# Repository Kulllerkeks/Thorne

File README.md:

# Thorne keyboard

The Thorne keyboard is a split keyboard with 3x6 column staggered keys 
and 3 thumb keys, a variation of the [Corne](https://github.com/foostan/crkbd) Keyboard.

## Lineup

- corne-classic
  ([JP](corne-classic/doc/buildguide_jp.md)/[EN](corne-classic/doc/buildguide_en.md)):
  Corne for Cherry MX switches
- corne-cherry
  ([JP](corne-cherry/doc/buildguide_jp.md)/[EN](corne-cherry/doc/buildguide_en.md))
  ([tilting, JP](corne-cherry/doc/v2/buildguide_tilting_tenting_plate_jp.md)/[tilting, EN](corne-cherry/doc/v2/buildguide_tilting_tenting_plate_en.md)):
  Hotswappable Corne for Cherry MX switches by kailh PCB sockets.
- corne-chocolate
  ([JP](corne-chocolate/doc/buildguide_jp.md)/[EN](corne-chocolate/doc/buildguide_en.md)):
  Hotswappable Corne for Chocolate switches using Kailh PCB hot-swap sockets.
- corne-light
  ([JP](corne-light/doc/buildguide_jp.md)/[EN](corne-light/doc/buildguide_en.md)):
  Light-weight Corne (Easy build with a simple PCB).

## Photos

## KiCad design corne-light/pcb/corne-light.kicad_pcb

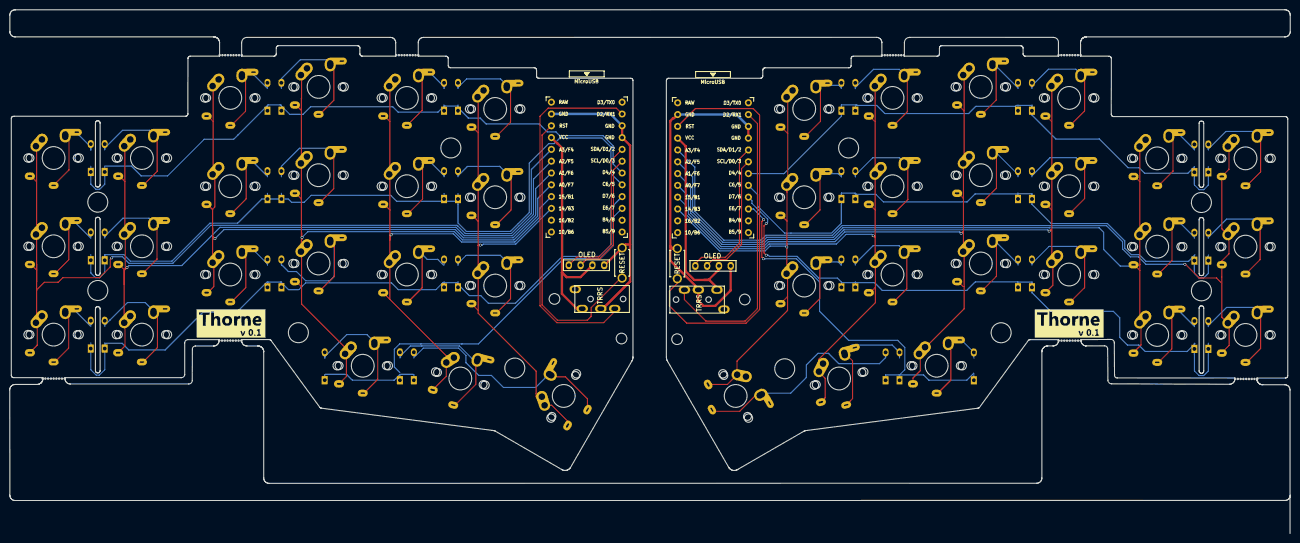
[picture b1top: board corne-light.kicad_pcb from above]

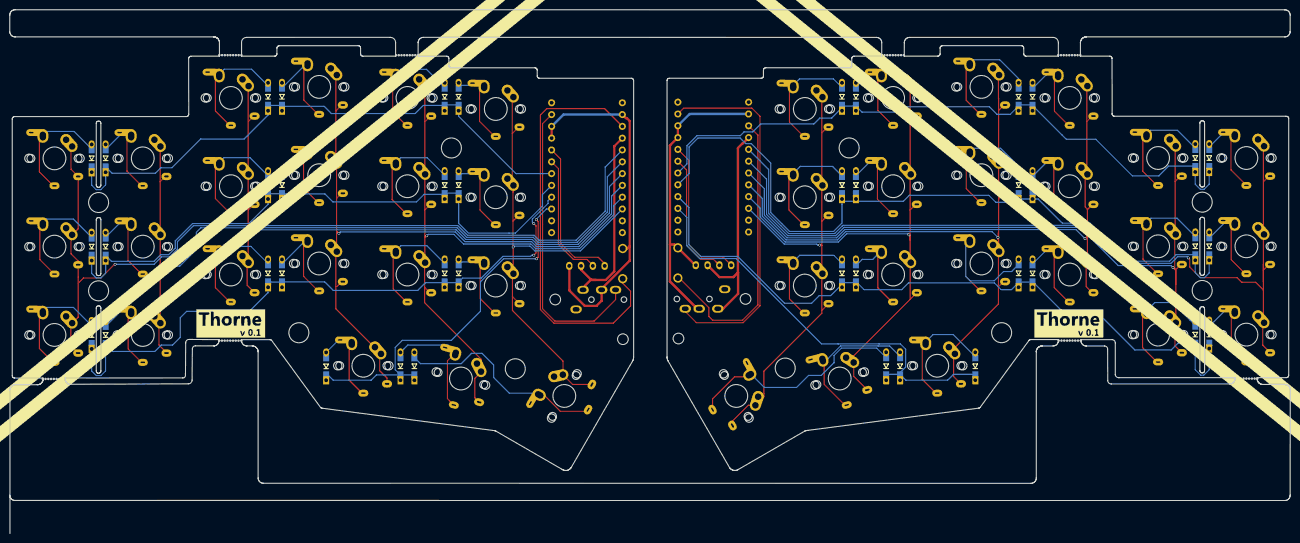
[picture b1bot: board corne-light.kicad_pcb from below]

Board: 2 copper layers, 275.5 x 112.7 mm, 114 parts (54 on the bottom side), 74 nets.

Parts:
D1, D2, D3, D4, D5, D6, D7, D8, D9, D10, D11, D12, D13, D14, D15, D16, D17, D18, D19, D20, D21, D22, D23, D24, D25, D26, D27, D28, D29, D30, D31, D32, D33, D34, D35, D36, D37, D38, D39, D40, D41, D42: D; D3_TH_SMD_v2
J1, J6: MJ-4PP-9; MJ-4PP-9_1side
J2, J7: OLED; OLED_1side
J5, J5#2, J5#3, J5#4, J5#5, J5#6, J5#7, J5#8: Breakaway_Tabs
RSW1, RSW2: SW_PUSH; ResetSW_1side
Ref**: Val**; thread_m2
Ref**#2, Ref**#8, Ref**#9: Val**; thread_m2
Ref**#3, Ref**#4, Ref**#5, Ref**#6, Ref**#7, Ref**#10, Ref**#11, Ref**#12, Ref**#13, Ref**#14: Val**; spacer_m2
SW1, SW2, SW3, SW4, SW5, SW6, SW7, SW8, SW9, SW10, SW11, SW12, SW13, SW14, SW15, SW16, SW17, SW18, SW19, SW20, SW22, SW23, SW24, SW25, SW26, SW27, SW28, SW29, SW30, SW31, SW32, SW33, SW34, SW35, SW36, SW37, SW38, SW39, SW40, SW41: SW_PUSH; keyswitch_cherrymx_alps_choc12_1u
SW21, SW42: SW_PUSH; keyswitch_cherrymx_alps_choc12_1.5u
U1, U2: ProMicro; ProMicro_v3

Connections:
GND: J1.C, J2.4, RSW1.2, U1.3, U1.4, U1.23
GNDA: J6.C, J7.4, RSW2.2, U2.3, U2.4, U2.23
unnamed: D1.2, SW1.2
unnamed: D2.2, SW2.2
unnamed: D3.2, SW3.2
unnamed: D4.2, SW4.2
unnamed: D5.2, SW5.2
unnamed: D6.2, SW6.2
unnamed: D7.2, SW7.2
unnamed: D8.2, SW8.2
unnamed: D9.2, SW9.2
unnamed: D10.2, SW10.2
unnamed: D11.2, SW11.2
unnamed: D12.2, SW12.2
unnamed: D13.2, SW13.2
unnamed: D14.2, SW14.2
unnamed: D15.2, SW15.2
unnamed: D16.2, SW16.2
unnamed: D17.2, SW17.2
unnamed: D18.2, SW18.2
unnamed: D19.2, SW19.2
unnamed: D20.2, SW20.2
unnamed: D21.2, SW21.2
unnamed: D22.2, SW22.2
unnamed: D23.2, SW23.2
unnamed: D24.2, SW24.2
unnamed: D25.2, SW25.2
unnamed: D26.2, SW26.2
unnamed: D27.2, SW27.2
unnamed: D28.2, SW28.2
unnamed: D29.2, SW29.2
unnamed: D30.2, SW30.2
unnamed: D31.2, SW31.2
unnamed: D32.2, SW32.2
unnamed: D33.2, SW33.2
unnamed: D34.2, SW34.2
unnamed: D35.2, SW35.2
unnamed: D36.2, SW36.2
unnamed: D37.2, SW37.2
unnamed: D38.2, SW38.2
unnamed: D39.2, SW39.2
unnamed: D40.2, SW40.2
unnamed: D41.2, SW41.2
unnamed: D42.2, SW42.2
SCL: J2.2, U1.6
SCL_r: J7.2, U2.6
SDA: J2.1, U1.5
SDA_r: J7.1, U2.5
VCC: J1.D, J2.3, U1.21
VDD: J6.D, J7.3, U2.21
col0: SW1.1, SW7.1, SW13.1, U1.20
col0_r: SW22.1, SW28.1, SW34.1, U2.20
col1: SW2.1, SW8.1, SW14.1, U1.19
col1_r: SW23.1, SW29.1, SW35.1, U2.19
col2: SW3.1, SW9.1, SW15.1, U1.18
col2_r: SW24.1, SW30.1, SW36.1, U2.18
col3: SW4.1, SW10.1, SW16.1, SW19.1, U1.17
col3_r: SW25.1, SW31.1, SW37.1, SW40.1, U2.17
col4: SW5.1, SW11.1, SW17.1, SW20.1, U1.16
col4_r: SW26.1, SW32.1, SW38.1, SW41.1, U2.16
col5: SW6.1, SW12.1, SW18.1, SW21.1, U1.15
col5_r: SW27.1, SW33.1, SW39.1, SW42.1, U2.15
data: J1.B, U1.2
data_r: J6.B, U2.2
reset: RSW1.1, U1.22
reset_r: RSW2.1, U2.22
row0: D1.1, D2.1, D3.1, D4.1, D5.1, D6.1, U1.7
row0_r: D22.1, D23.1, D24.1, D25.1, D26.1, D27.1, U2.7
row1: D7.1, D8.1, D9.1, D10.1, D11.1, D12.1, U1.8
row1_r: D28.1, D29.1, D30.1, D31.1, D32.1, D33.1, U2.8
row2: D13.1, D14.1, D15.1, D16.1, D17.1, D18.1, U1.9
row2_r: D34.1, D35.1, D36.1, D37.1, D38.1, D39.1, U2.9
row3: D19.1, D20.1, D21.1, U1.10
row3_r: D40.1, D41.1, D42.1, U2.10

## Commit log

2023-01-31 Changed Landing page
2023-01-31 Changed desciption
2023-01-31 Changed stagger of pinky collumns
2023-02-02 added placeholder keymap file
2023-02-02 added artwork
2023-02-02 changed layout, still WIP
2023-06-07 test
    test
2023-06-07 test removed
